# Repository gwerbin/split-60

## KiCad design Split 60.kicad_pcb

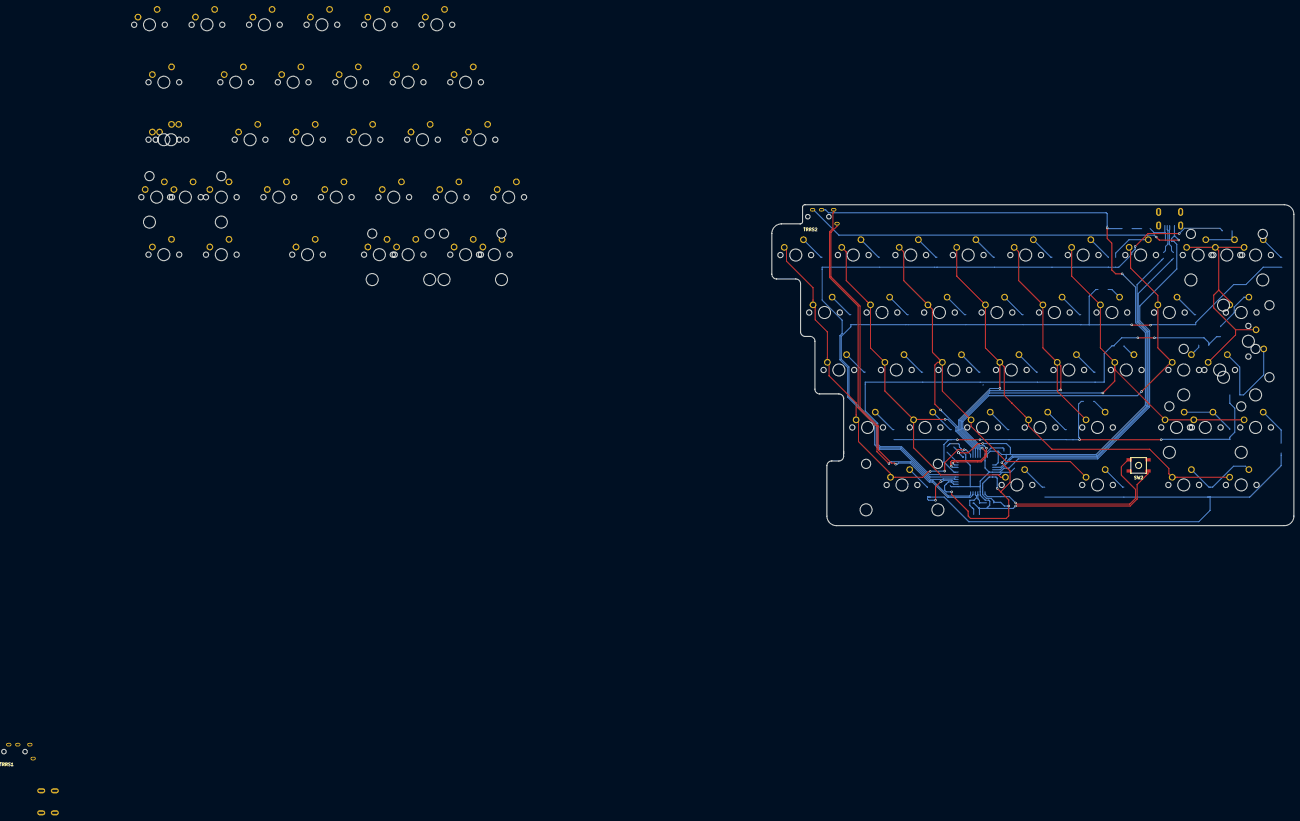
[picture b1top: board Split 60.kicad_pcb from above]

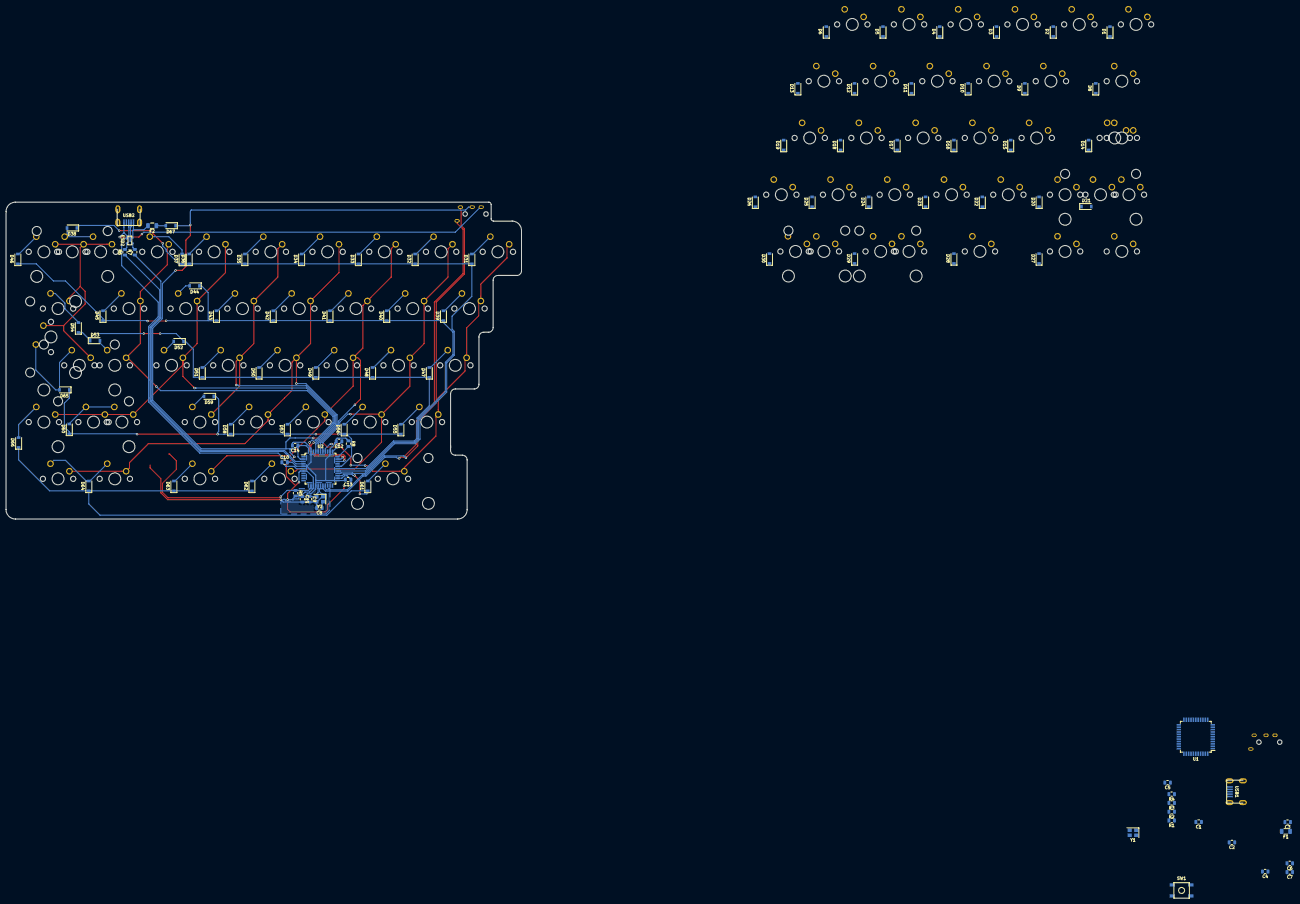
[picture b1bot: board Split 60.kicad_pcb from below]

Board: 2 copper layers, 173.0 x 106.4 mm, 175 parts (98 on the bottom side), 115 nets.

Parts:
C1, C2, C8, C9: 22pF; C_0805_2012Metric
C3, C10: 1uF; C_0805_2012Metric
C4, C5, C6, C11, C12, C13: 0.1uF; C_0805_2012Metric
C7, C14: 10uF; C_0805_2012Metric
D1, D2, D3, D4, D5, D6, D8, D9, D10, D11, D12, D13, D14, D15, D16, D17, D18, D19, D20, D21, D22, D23, D24, D25, D26, D27, D28, D29, D30, D31, D32, D33, D34, D35, D36, D37, D38, D39, D40, D41, D42, D43, D44, D45, D46, D47, D48, D49, D50, D51, D52, D53, D54, D55, D56, D57, D58, D59, D60, D61, D62, D63, D64, D65, D66: D_Small; D_SOD-123
D67: D_Schottky; D_SOD-123-Pretty
ESD2: PRTR5V0U2X; SOT143B
F1, F2: 500mA; Fuse_1206_3216Metric
MX_11, MX_21, MX_31, MX_41, MX_51, MX_61, MX_71, MX_81, MX_91: MX-NoLED; MXOnly-1U-NoLED
MX_A1: MX-NoLED; MXOnly-1U-NoLED
MX_B1: MX-NoLED; MXOnly-1U-NoLED
MX_Backslash1: MX-NoLED; MXOnly-1.5U-NoLED
MX_Bksp1: MX-NoLED; MXOnly-2U-NoLED
MX_C1: MX-NoLED; MXOnly-1U-NoLED
MX_Caps1: MX-NoLED; MXOnly-1.75U-NoLED
MX_Caps2: MX-NoLED; MXOnly-1.5U-NoLED
MX_Colon1: MX-NoLED; MXOnly-1U-NoLED
MX_Comma1: MX-NoLED; MXOnly-1U-NoLED
MX_D1: MX-NoLED; MXOnly-1U-NoLED
MX_E1: MX-NoLED; MXOnly-1U-NoLED
MX_Enter1: MX-NoLED; MXOnly-2.25U-NoLED
MX_Enter2: MX-NoLED; MXOnly-ISO-ROTATED-ReversedStabilizers-NoLED
MX_Esc1: MX-NoLED; MXOnly-1U-NoLED
MX_F1: MX-NoLED; MXOnly-1U-NoLED
MX_Fn1: MX-NoLED; MXOnly-1U-NoLED
MX_G1: MX-NoLED; MXOnly-1U-NoLED
MX_H1: MX-NoLED; MXOnly-1U-NoLED
MX_HhkbBackslash1: MX-NoLED; MXOnly-1U-NoLED
MX_HhkbTilde1: MX-NoLED; MXOnly-1U-NoLED
MX_I1: MX-NoLED; MXOnly-1U-NoLED
MX_IsoHash1: MX-NoLED; MXOnly-1U-NoLED
MX_IsoSlash1: MX-NoLED; MXOnly-1U-NoLED
MX_J1: MX-NoLED; MXOnly-1U-NoLED
MX_K1: MX-NoLED; MXOnly-1U-NoLED
MX_L1: MX-NoLED; MXOnly-1U-NoLED
MX_LAlt1: MX-NoLED; MXOnly-1.5U-NoLED
MX_LBrace1: MX-NoLED; MXOnly-1U-NoLED
MX_LCtrl1, MX_LCtrl2: MX-NoLED; MXOnly-1.5U-NoLED
MX_LExtra1, MX_LExtra2: MX-NoLED; MXOnly-1U-NoLED
MX_LShift1: MX-NoLED; MXOnly-2.25U-NoLED
MX_LShift2: MX-NoLED; MXOnly-1.25U-NoLED
MX_LSpace1, MX_LSpace2: MX-NoLED; MXOnly-2U-NoLED
MX_M1: MX-NoLED; MXOnly-1U-NoLED
MX_Minus1: MX-NoLED; MXOnly-1U-NoLED
MX_N1: MX-NoLED; MXOnly-1U-NoLED
MX_O1: MX-NoLED; MXOnly-1U-NoLED
MX_P1: MX-NoLED; MXOnly-1U-NoLED
MX_Period1: MX-NoLED; MXOnly-1U-NoLED
MX_Plus1: MX-NoLED; MXOnly-1U-NoLED
MX_Q1: MX-NoLED; MXOnly-1U-NoLED
MX_Quote1: MX-NoLED; MXOnly-1U-NoLED
MX_R1: MX-NoLED; MXOnly-1U-NoLED
MX_RAlt1: MX-NoLED; MXOnly-1.5U-NoLED
MX_RBrace1: MX-NoLED; MXOnly-1U-NoLED
MX_RCtrl1, MX_RCtrl2: MX-NoLED; MXOnly-1.5U-NoLED
MX_RExtra1: MX-NoLED; MXOnly-1.25U-NoLED
MX_RShift1: MX-NoLED; MXOnly-2.75U-NoLED
MX_RShift2: MX-NoLED; MXOnly-1.75U-NoLED
MX_RSpace1: MX-NoLED; MXOnly-2.75U-NoLED
MX_S1: MX-NoLED; MXOnly-1U-NoLED
MX_Slash1: MX-NoLED; MXOnly-1U-NoLED
MX_T1: MX-NoLED; MXOnly-1U-NoLED
MX_Tab1: MX-NoLED; MXOnly-1.5U-NoLED
MX_U1: MX-NoLED; MXOnly-1U-NoLED
MX_V1: MX-NoLED; MXOnly-1U-NoLED
MX_W1: MX-NoLED; MXOnly-1U-NoLED
MX_X1: MX-NoLED; MXOnly-1U-NoLED
MX_Y1: MX-NoLED; MXOnly-1U-NoLED
MX_Z1: MX-NoLED; MXOnly-1U-NoLED
MX_Zero1: MX-NoLED; MXOnly-1U-NoLED
R1, R4, R5, R8: 10k; R_0805_2012Metric
R2, R3, R6, R7: 22; R_0805_2012Metric
SW1, SW2: SW_Push; SKQG-1155865
TRRS1, TRRS2: TRRS; PJ-3200B-4A
U1, U2: ATmega32U4-AU; TQFP-44_10x10mm_P0.8mm
USB1, USB2: Molex-0548190589
Y1, Y2: 16MHz; Crystal_SMD_3225-4Pin_3.2x2.5mm

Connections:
+5V: C4.1, C5.1, C6.1, C7.1, C11.1, C12.1, C13.1, C14.1, D67.1, F1.1, R1.2, R5.2, TRRS1.2, TRRS2.2, U1.2, U1.7, U1.14, U1.24, U1.34, U1.44, U2.2, U2.7, U2.14, U2.24, U2.34, U2.44
GND: C1.2, C2.2, C3.2, C4.2, C5.2, C6.2, C7.2, C8.2, C9.2, C10.2, C11.2, C12.2, C13.2, C14.2, ESD2.1, R4.1, R8.1, SW1.1, SW2.1, TRRS1.1, TRRS2.1, U1.5, U1.15, U1.23, U1.35, U1.43, U2.5, U2.15, U2.23, U2.35, U2.43, USB1.1, USB2.1, Y1.1, Y1.3, Y2.1, Y2.3
L_C0: MX_Caps1.1, MX_Caps2.1, MX_Esc1.1, MX_LCtrl1.1, MX_LCtrl2.1, MX_LShift1.1, MX_LShift2.1, MX_Tab1.1
L_C1: MX_11.1, MX_A1.1, MX_IsoSlash1.1, MX_LAlt1.1, MX_Q1.1
L_C2: MX_21.1, MX_LExtra2.1, MX_LSpace1.1, MX_S1.1, MX_W1.1, MX_Z1.1
L_C3: MX_31.1, MX_D1.1, MX_E1.1, MX_X1.1
L_C4: MX_41.1, MX_C1.1, MX_F1.1, MX_LExtra1.1, MX_LSpace2.1, MX_R1.1
L_C5: MX_51.1, MX_B1.1, MX_G1.1, MX_T1.1, MX_V1.1
L_D+: R2.2, USB1.3
L_D-: R3.2, USB1.4
L_R0: D1.1, D2.1, D3.1, D4.1, D5.1, D6.1
L_R1: D8.1, D9.1, D10.1, D11.1, D12.1, D13.1
L_R2: D14.1, D15.1, D16.1, D17.1, D18.1, D19.1
L_R3: D20.1, D21.1, D22.1, D23.1, D24.1, D25.1
L_R4: D26.1, D27.1, D28.1, D29.1, D30.1
L_SCL: TRRS1.4, U1.18
L_SDA: TRRS1.3, U1.19
unnamed: C1.1, U1.17, Y1.4
unnamed: C2.1, U1.16, Y1.2
unnamed: C3.1, U1.6
unnamed: C8.1, U2.17, Y2.4
unnamed: C9.1, U2.16, Y2.2
unnamed: C10.1, U2.6
unnamed: D1.2, MX_Esc1.2
unnamed: D2.2, MX_11.2
unnamed: D3.2, MX_21.2
unnamed: D4.2, MX_31.2
unnamed: D5.2, MX_41.2
unnamed: D6.2, MX_51.2
unnamed: D8.2, MX_Tab1.2
unnamed: D9.2, MX_Q1.2
unnamed: D10.2, MX_W1.2
unnamed: D11.2, MX_E1.2
unnamed: D12.2, MX_R1.2
unnamed: D13.2, MX_T1.2
unnamed: D14.2, MX_Caps1.2, MX_Caps2.2
unnamed: D15.2, MX_A1.2
unnamed: D16.2, MX_S1.2
unnamed: D17.2, MX_D1.2
unnamed: D18.2, MX_F1.2
unnamed: D19.2, MX_G1.2
unnamed: D20.2, MX_IsoSlash1.2
unnamed: D21.2, MX_LShift1.2, MX_LShift2.2
unnamed: D22.2, MX_Z1.2
unnamed: D23.2, MX_X1.2
unnamed: D24.2, MX_C1.2
unnamed: D25.2, MX_V1.2
unnamed: D26.2, MX_B1.2
unnamed: D27.2, MX_LCtrl1.2, MX_LCtrl2.2
unnamed: D28.2, MX_LAlt1.2
unnamed: D29.2, MX_LExtra2.2, MX_LSpace1.2
unnamed: D30.2, MX_LExtra1.2, MX_LSpace2.2
unnamed: D31.2, MX_61.2
unnamed: D32.2, MX_71.2
unnamed: D33.2, MX_81.2
unnamed: D34.2, MX_91.2
unnamed: D35.2, MX_Zero1.2
unnamed: D36.2, MX_Minus1.2
unnamed: D37.2, MX_Plus1.2
unnamed: D38.2, MX_Bksp1.2, MX_HhkbBackslash1.2
unnamed: D39.2, MX_Y1.2
unnamed: D40.2, MX_U1.2
unnamed: D41.2, MX_I1.2
unnamed: D42.2, MX_O1.2
unnamed: D43.2, MX_P1.2
unnamed: D44.2, MX_LBrace1.2
unnamed: D45.2, MX_RBrace1.2
unnamed: D46.2, MX_HhkbTilde1.2
unnamed: D47.2, MX_H1.2
unnamed: D48.2, MX_J1.2
unnamed: D49.2, MX_K1.2
unnamed: D50.2, MX_L1.2
unnamed: D51.2, MX_Colon1.2
unnamed: D52.2, MX_Quote1.2
unnamed: D53.2, MX_IsoHash1.2
unnamed: D54.2, MX_Backslash1.2
unnamed: D55.2, MX_N1.2
unnamed: D56.2, MX_M1.2
unnamed: D57.2, MX_Comma1.2
unnamed: D58.2, MX_Period1.2
unnamed: D59.2, MX_Slash1.2
unnamed: D60.2, MX_RShift1.2, MX_RShift2.2
unnamed: D61.2, MX_RSpace1.2
unnamed: D62.2, MX_RExtra1.2
unnamed: D63.2, MX_RAlt1.2
unnamed: D64.2, MX_RCtrl1.2, MX_RCtrl2.2
unnamed: D65.2, MX_Enter1.2, MX_Enter2.2
unnamed: D66.2, MX_Fn1.2
unnamed: D67.2, F2.1
unnamed: ESD2.2, R6.2, USB2.3
unnamed: ESD2.3, R7.2, USB2.4
unnamed: R1.1, SW1.2, U1.13
unnamed: R2.1, U1.4
unnamed: R3.1, U1.3
unnamed: R4.2, U1.33
unnamed: R8.2, U2.33
R_C0: MX_61.1, MX_H1.1, MX_N1.1, MX_RSpace1.1, MX_Y1.1, U2.37
R_C1: MX_71.1, MX_J1.1, MX_M1.1, MX_RExtra1.1, MX_U1.1, U2.38
R_C2: MX_81.1, MX_Comma1.1, MX_I1.1, MX_K1.1, MX_RAlt1.1, U2.39
R_C3: MX_91.1, MX_L1.1, MX_O1.1, MX_Period1.1, MX_RCtrl1.1, MX_RCtrl2.1, U2.40
R_C4: MX_Colon1.1, MX_P1.1, MX_Slash1.1, MX_Zero1.1, U2.41
R_C5: MX_Fn1.1, MX_LBrace1.1, MX_Minus1.1, MX_Quote1.1, MX_RShift1.1, MX_RShift2.1, U2.31
R_C6: MX_IsoHash1.1, MX_Plus1.1, MX_RBrace1.1, U2.32
R_C7: MX_Backslash1.1, MX_Bksp1.1, MX_Enter1.1, MX_Enter2.1, MX_HhkbBackslash1.1, MX_HhkbTilde1.1
R_D+: R6.1, U2.4
R_D-: R7.1, U2.3
R_R0: D31.1, D32.1, D33.1, D34.1, D35.1, D36.1, D37.1, D38.1, U2.26
R_R1: D39.1, D40.1, D41.1, D42.1, D43.1, D44.1, D45.1, D46.1, U2.27
R_R2: D47.1, D48.1, D49.1, D50.1, D51.1, D52.1, D53.1, D54.1, U2.28
R_R3: D55.1, D56.1, D57.1, D58.1, D59.1, D60.1, D65.1, U2.29
R_R4: D61.1, D62.1, D63.1, D64.1, D66.1, U2.25
R_Reset: R5.1, SW2.2, U2.13
R_SCL: TRRS2.4, U2.18
R_SDA: TRRS2.3, U2.19
VCC: ESD2.4, F1.2, F2.2, USB1.5, USB2.5

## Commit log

2020-03-06 Add external libs
2020-03-06 Add empty project files
2020-03-06 Finish switch schematic
2020-03-06 Associate footprints
2020-03-06 Fix MX numbering
2020-03-06 Lay out mod footprints & fix association mistakes
2020-03-06 Place switch diodes
2020-03-06 WIP routing
2020-03-09 Shitty work in progress
2020-03-09 Rename to split 60, tweak routing
